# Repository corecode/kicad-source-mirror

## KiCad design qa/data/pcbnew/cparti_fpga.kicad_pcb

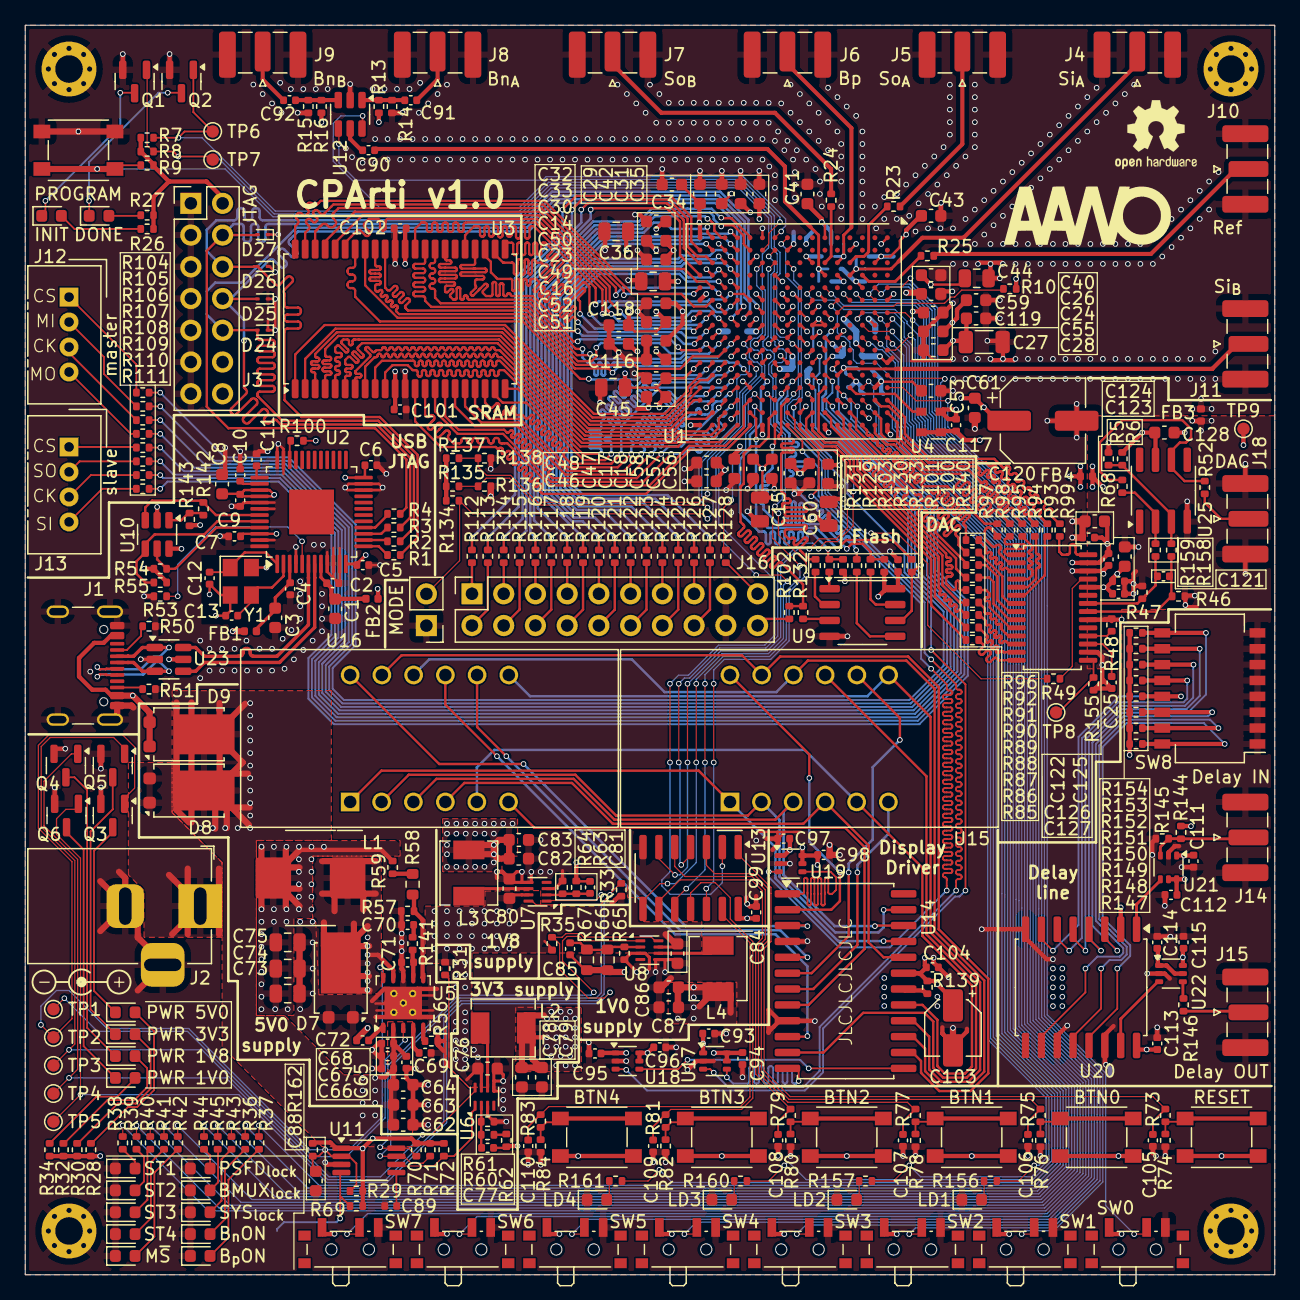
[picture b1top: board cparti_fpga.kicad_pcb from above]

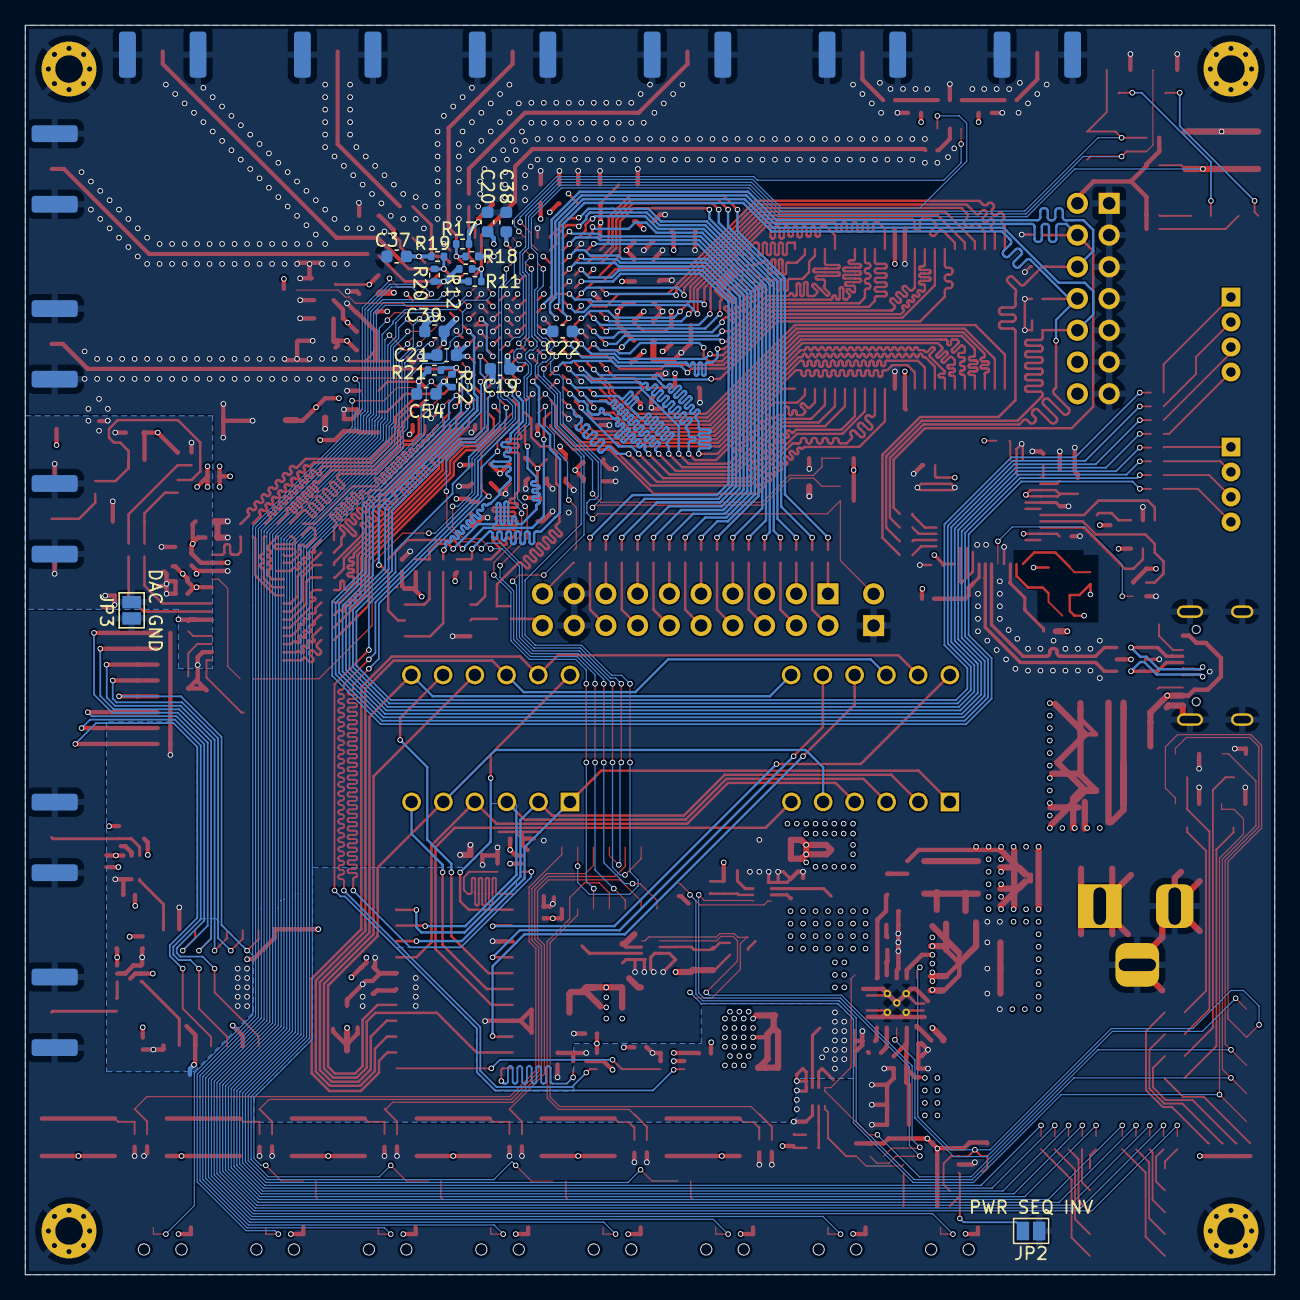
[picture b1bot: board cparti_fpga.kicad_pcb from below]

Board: 4 copper layers, 100.0 x 100.0 mm, 410 parts (18 on the bottom side), 333 nets.

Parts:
BTN0, BTN1, BTN2, BTN3, BTN4: SW_Push; SW_Push_TSC015A035_4.5x4.5mm_H4.5mm
BTN6: RESET; SW_Push_TSC015A035_4.5x4.5mm_H4.5mm
BTN7: PROGRAM; SW_Push_TSC015A035_4.5x4.5mm_H4.5mm
C1, C3, C8, C17, C24, C34, C35, C42, C43, C46, C47, C58, C59, C61, C116, C118: 4.7u; C_0603_1608Metric
C2, C4, C5, C6, C7, C9, C10, C11, C25, C72, C93, C94, C95, C96, C97, C98, C99, C100, C101, C102, C104, C105, C106, C107, C108, C109, C110, C111, C112, C113, C114, C115, C117, C122, C123, C126, C127: 100n; C_0402_1005Metric
C12, C13: 20p; C_0402_1005Metric
C14, C15, C36, C44, C45, C60, C73, C74, C75: 47u; C_0805_2012Metric
C16, C18, C19, C20, C21, C22, C23, C26, C28, C29, C30, C31, C32, C33, C37, C38, C39, C40, C41, C48, C49, C50, C51, C52, C53, C54, C55, C56, C57, C119: 470n; C_0603_1608Metric
C27: 100u; C_1206_3216Metric
C62, C63, C64, C76, C78, C79, C80, C82, C83, C84, C86, C87, C88, C124, C125, C128: 10u; C_0603_1608Metric
C65, C66, C67, C68: 2u2; C_0402_1005Metric
C69, C89, C90, C91, C92: 10n; C_0402_1005Metric
C70: 4n7; C_0402_1005Metric
C71: 47p; C_0402_1005Metric
C77, C81, C85: 120p; C_0402_1005Metric
C103: 10u; CP_Elec_4x5.4
C120: 330u; CP_Elec_6.3x7.7
C121: C_0402_1005Metric
D1: INIT; LED_0603_1608Metric
D2: DONE; LED_0603_1608Metric
D3: PWR 5V0; LED_0603_1608Metric
D4: PWR 3V3; LED_0603_1608Metric
D5: PWR 1V8; LED_0603_1608Metric
D6: PWR 1V0; LED_0603_1608Metric
D7, D8, D9: PDS760; TO-277B
D10: B_{n}ON; LED_0603_1608Metric
D11: B_{p}ON; LED_0603_1608Metric
D12: ST1; LED_0603_1608Metric
D13: ST2; LED_0603_1608Metric
D14: ST3; LED_0603_1608Metric
D15: ST4; LED_0603_1608Metric
D16: M~{S}; LED_0603_1608Metric
D17: SYS_{lock}; LED_0603_1608Metric
D18: PSFD_{lock}; LED_0603_1608Metric
D19: BMUX_{lock}; LED_0603_1608Metric
D20: LD1; LED_0603_1608Metric
D21: LD2; LED_0603_1608Metric
D22: LD3; LED_0603_1608Metric
D23: LD4; LED_0603_1608Metric
D24, D25, D26, D27: ESD9B3.3ST5G; D_SOD-923
FB1, FB2, FB3, FB4: BLM15AG601SN1D; L_0402_1005Metric
H1, H2, H3, H4: MountingHole_Pad; MountingHole_2.2mm_M2_Pad_Via
J1: USB_C_Receptacle_USB2.0_16P; USB_C_Receptacle_GCT_USB4105-xx-A_16P_TopMnt_Horizontal
J2: Barrel_Jack_Switch; BarrelJack_Horizontal
J3: JTAG; PinHeader_2x07_P2.54mm_Vertical
J4: Si_{A}; SMA_Samtec_SMA-J-P-H-ST-EM1_EdgeMount
J5: So_{A}; SMA_Samtec_SMA-J-P-H-ST-EM1_EdgeMount
J6: Bp; SMA_Samtec_SMA-J-P-H-ST-EM1_EdgeMount
J7: So_{B}; SMA_Samtec_SMA-J-P-H-ST-EM1_EdgeMount
J8: Bn_{A}; SMA_Samtec_SMA-J-P-H-ST-EM1_EdgeMount
J9: Bn_{B}; SMA_Samtec_SMA-J-P-H-ST-EM1_EdgeMount
J10: Ref; SMA_Samtec_SMA-J-P-H-ST-EM1_EdgeMount
J11: Si_{B}; SMA_Samtec_SMA-J-P-H-ST-EM1_EdgeMount
J12: master; NS-Tech_Grove_1x04_P2mm_Vertical
J13: slave; NS-Tech_Grove_1x04_P2mm_Vertical
J14: Delay IN; SMA_Samtec_SMA-J-P-H-ST-EM1_EdgeMount
J15: Delay OUT; SMA_Samtec_SMA-J-P-H-ST-EM1_EdgeMount
J16: Conn_02x10_Odd_Even; PinSocket_2x10_P2.54mm_Vertical
J18: DAC; SMA_Samtec_SMA-J-P-H-ST-EM1_EdgeMount
JP1: MODE; PinHeader_1x02_P2.54mm_Vertical
JP2: PWR SEQ INV; SolderJumper-2_P1.3mm_Open_Pad1.0x1.5mm
JP3: DAC GND; SolderJumper-2_P1.3mm_Open_Pad1.0x1.5mm
L1: 6.8uH/6.8A; L_TDK_SPM7054VT
L2, L3, L4: 470nH/7.6A; L_Chilisin_BMRx00040412
NT1, NT2, NT3, NT4: NetTie_2; NetTie-2_SMD_Pad0.2355mm
Q1, Q2, Q3, Q4, Q5, Q6: 2N7002; SOT-23
R1, R2, R3, R4, R49, R85, R86, R87, R88, R89, R90, R91, R92, R93, R94, R95, R96, R97, R98, R99, R104, R105, R106, R107, R108, R109, R110, R111: 22R; R_0402_1005Metric
R5, R6, R26, R27, R28, R30, R32, R34, R59, R128, R134: 1k; R_0402_1005Metric
R7, R36, R37, R38, R39, R40, R41, R42, R43, R44, R45, R156, R157, R160, R161: 330R; R_0402_1005Metric
R8, R9, R10, R103: 4k7; R_0402_1005Metric
R11, R12, R13, R14, R15, R16, R17, R18, R19, R20, R21, R22, R112, R113, R114, R115, R116, R117, R118, R119, R120, R121, R122, R123, R124, R125, R126, R127, R129, R130, R131, R132, R133, R144, R145: 100; R_0402_1005Metric
R23, R24, R25, R52, R135, R136, R137, R138, R146: 0; R_0402_1005Metric
R29, R31, R33, R35, R54, R55, R69, R73, R74, R75, R76, R77, R78, R79, R80, R81, R82, R83, R84, R100, R139, R143, R147, R148, R149, R150, R151, R152, R153, R154, R155: 10k; R_0402_1005Metric
R46, R47: 25R5; R_0402_1005Metric
R48, R101, R102, R142: 2k; R_0402_1005Metric
R50, R51: 5k1; R_0402_1005Metric
R53: 12k/1%; R_0402_1005Metric
R56: 243k; R_0402_1005Metric
R57: 12k; R_0402_1005Metric
R58: 62k; R_0603_1608Metric
R60, R64, R70, R71, R72, R162: 100k; R_0402_1005Metric
R61: 150k; R_0402_1005Metric
R62: 300k; R_0402_1005Metric
R63: 200k; R_0402_1005Metric
R65: 120k; R_0402_1005Metric
R66, R67: 160k; R_0603_1608Metric
R68: 500; R_0402_1005Metric
R140: 49R9; R_0402_1005Metric
R141: 16k9; R_0402_1005Metric
R158, R159: 226; R_0402_1005Metric
SW0, SW1, SW2, SW3, SW4, SW5, SW6, SW7: SW_SPDT; SW_SPDT_PCM12
SW8: SW_DIP_x08; SW_DIP_SPSTx08_Slide_KingTek_DSHP08TS_W7.62mm_P1.27mm
TP1, TP2, TP3, TP4, TP5, TP6, TP7, TP8, TP9: TestPoint; TestPoint_Pad_D1.0mm
U1: XC7A50T-FTG256; Xilinx_FTG256
U2: FT232H; LQFP-48-1EP_7x7mm_P0.5mm_EP3.6x3.6mm
U3: IS61WV25616EDBLL; TSOP-II-44_10.16x18.41mm_P0.8mm
U4: ASDM1-24MHz; Oscillator_SMD_Abracon_ASDMB-4Pin_2.5x2.0mm
U5: TPS54561; Texas_S-PWSON-N10_4x4mm_ThermalVias
U6, U7, U8: TPS62823DLC; Texas_VSON-HR-8_1.5x2mm_P0.5mm
U9: MX25L3233FM1; SOP-8_3.9x4.9mm_P1.27mm
U10: 93LC56BT-I/OT; SOT-23-6
U11: LM3881; Texas_S-PDSO-G8_3x3mm_P0.65mm
U12: AS169-73LF; SOT-23-6
U13: 74HC14; SO-14_3.9x8.65mm_P1.27mm
U14: MAX7219; SOIC-24W_7.5x15.4mm_P1.27mm
U15, U16: XLITX 3641AS; XLITX_3641AS
U17, U18, U19, U21, U22: SN74LVC1T45DCK; SOT-363_SC-70-6
U20: DS1023; SOIC-16W_7.5x10.3mm_P1.27mm
U23: USBLC6-2SC6; SOT-23-6
U24: AD9744; TSSOP-28_4.4x9.7mm_P0.65mm
U25: OPA356AID; SOIC-8_3.9x4.9mm_P1.27mm
Y1: 12 MHz; Crystal_SMD_3225-4Pin_3.2x2.5mm

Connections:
7SEG_{CLK}: U1.H12 (IO_L20P_T3_A20_15), U18.3 (A)
7SEG_{DIN}: U1.J15 (IO_L23P_T3_FOE_B_15), U19.3 (A)
7SEG_{LOAD}: U1.J16 (IO_L23N_T3_FWE_B_15), U17.3 (A)
+1V0: C20.2, C21.2, C22.2, C23.2, C24.2, C27.2, C28.2, C61.2, C85.2, C86.2, C87.2, C118.2, C119.2, C120.1, L4.2, R66.2, R67.2, U1.E10 (VCCBRAM), U1.F7 (VCCINT), U1.F9 (VCCINT), U1.F11 (VCCBRAM), U1.G6 (VCCINT), U1.H9 (VCCINT), U1.J6 (VCCINT), U1.K9 (VCCINT), U1.L8 (VCCINT)
+1V8: C15.2, C16.2, C17.2, C18.2, C19.2, C26.1, C81.2, C82.2, C83.2, C116.2, L3.2, R63.2, U1.F8 (VCCBATT_0), U1.G8 (VCCADC_0), U1.G10 (VCCAUX), U1.J10 (VCCAUX), U1.K11 (VCCAUX), U1.L10 (VCCAUX)
+3.3VA: C125.2, C126.1, C127.1, C128.2, FB4.2, R6.1, TP9.1, U24.24 (AVDD), U25.7 (V+)
+3V3: BTN0.1, BTN1.1, BTN2.1, BTN3.1, BTN4.1, BTN6.1, C5.2, C6.2, C7.2, C8.2, C9.2, C14.1, C29.2, C30.2, C31.2, C32.2, C33.2, C34.2, C35.2, C36.2, C37.2, C38.2, C39.2, C40.2, C41.2, C42.2, C43.2, C44.2, C45.2, C46.2, C47.2, C48.2, C49.2, C50.2, C51.2, C52.2, C53.2, C54.2, C55.2, C56.2, C57.2, C58.2, C59.2, C60.2, C77.2, C78.2, C79.2, C93.2, C95.2, C97.2, C99.2, C100.2, C101.2, C102.2, C111.2, C115.2, C117.2, C122.1, C123.1, C124.2, FB1.1, FB2.1, FB4.1, J3.2, J16.19, J16.20, L2.2, R7.2, R8.2, R9.2, R10.2, R11.1, R13.1, R15.1, R17.1, R19.1, R21.1, R26.2, R27.2, R28.2, R30.2, R32.2, R34.2, R54.1, R55.1, R62.2, R100.2, R101.2, R102.2, R103.2, R128.1, R134.2, R135.1, R137.1, R143.1, R144.1, SW0.1 (A), SW1.1 (A), SW2.1 (A), SW3.1 (A), SW4.1 (A), SW5.1 (A), SW6.1 (A), SW7.1 (A), U1.A6 (VCCO_35), U1.A16 (VCCO_15), U1.B3 (VCCO_35), U1.B13 (VCCO_15), U1.C10 (VCCO_15), U1.D7 (VCCO_35), U1.E4 (VCCO_35), U1.E14 (VCCO_15), U1.F1 (VCCO_35), U1.H15 (VCCO_15), U1.J2 (VCCO_35), U1.J12 (VCCO_15), U1.L6 (VCCO_0), U1.L16 (VCCO_14), U1.M3 (VCCO_34), U1.M13 (VCCO_14), U1.N10 (VCCO_14), U1.P7 (VCCO_14), U1.R4 (VCCO_34), U1.R14 (VCCO_14), U1.T1 (VCCO_34), U1.T11 (VCCO_14), U2.12 (VCCIO), U2.24 (VCCIO), U2.39 (VCCD), U2.40 (VREGIN), U2.46 (VCCIO), U3.11 (VDD), U3.33 (VDD), U4.1 (Standby), U4.4 (VDD), U9.8 (VCC), U10.6 (VCC), U13.14 (VCC), U17.1 (VCCA), U18.1 (VCCA), U19.1 (VCCA), U21.1 (VCCA), U22.6 (VCCB), U24.27 (DVDD)
+5V: C73.2, C74.2, C75.2, C76.2, C80.2, C84.2, C94.2, C96.2, C98.2, C103.1, C104.2, C112.2, C113.2, C114.2, L1.2, R29.1, R31.1, R33.1, R35.1, R59.2, R69.2, R70.2, R71.2, R72.2, R139.1, R147.2, R148.2, R149.2, R150.2, R151.2, R152.2, R153.2, R154.2, R162.2, U6.7 (VIN), U7.7 (VIN), U8.7 (VIN), U11.1 (VCC), U14.19 (V+), U17.5 (DIR), U17.6 (VCCB), U18.5 (DIR), U18.6 (VCCB), U19.5 (DIR), U19.6 (VCCB), U20.2 (LE), U20.16 (VCC), U21.5 (DIR), U21.6 (VCCB), U22.1 (VCCA), U22.5 (DIR)
/DAC/DAC_OPAMP_O: R52.2, R68.2, U25.6
/DAC/DAC_OPAMP_O_R: J18.1 (In), R52.1
/DAC/IOUTA: C121.2, R47.1, R159.1, U24.22 (IOUTA)
/DAC/IOUTA_R: R68.1, R159.2, U25.2 (-)
/DAC/IOUTB: C121.1, R46.1, R158.1, U24.21 (IOUTB)
/DAC/IOUTB_R: R5.2, R6.2, R158.2, U25.3 (+)
/DAC/R_DAC_CLK: R99.2, U24.28 (CLK)
/DAC/R_DAC_D0: R85.2, U24.14 (D0)
/DAC/R_DAC_D1: R86.2, U24.13 (D1)
/DAC/R_DAC_D2: R87.2, U24.12 (D2)
/DAC/R_DAC_D3: R88.2, U24.11 (D3)
/DAC/R_DAC_D4: R89.2, U24.10 (D4)
/DAC/R_DAC_D5: R90.2, U24.9 (D5)
/DAC/R_DAC_D6: R91.2, U24.8 (D6)
/DAC/R_DAC_D7: R92.2, U24.7 (D7)
/DAC/R_DAC_D8: R93.2, U24.6 (D8)
/DAC/R_DAC_D9: R94.2, U24.5 (D9)
/DAC/R_DAC_D10: R95.2, U24.4 (D10)
/DAC/R_DAC_D11: R96.2, U24.3 (D11)
/DAC/R_DAC_D12: R97.2, U24.2 (D12)
/DAC/R_DAC_D13: R98.2, U24.1 (D13)
/DAC/R_DAC_MODE: R49.2, U24.25 (MODE)
/DAC/SLEEP: R155.2, TP8.1, U24.15 (SLEEP)
/FPGA banks 14-15/EMCCLK: R140.2, U1.M15 (IO_L3N_T0_DQS_EMCCLK_14)
/FPGA banks 14-15/SPIm_MISO_R: J12.2, R105.2
/FPGA banks 14-15/SPIm_MOSI_R: J12.4, R107.2
/FPGA banks 14-15/SPIm_SCK_R: J12.3, R106.2
/FPGA banks 14-15/SPIm_~CS_R: J12.1, R104.2
/FPGA banks 14-15/SPIs_MISO_R: J13.2, R109.2
/FPGA banks 14-15/SPIs_MOSI_R: J13.4, R111.2
/FPGA banks 14-15/SPIs_SCK_R: J13.3, R110.2
/FPGA banks 14-15/SPIs_~CS_R: J13.1, R108.2
/FPGA banks 34-35/IO_0: R112.1, U1.T2 (IO_L8N_T1_34)
/FPGA banks 34-35/IO_0_R: J16.1, R112.2
/FPGA banks 34-35/IO_1: R113.1, U1.R3 (IO_L8P_T1_34)
/FPGA banks 34-35/IO_1_R: J16.2, R113.2
/FPGA banks 34-35/IO_2: R114.1, U1.T3 (IO_L9N_T1_DQS_34)
/FPGA banks 34-35/IO_2_R: J16.3, R114.2
/FPGA banks 34-35/IO_3: R115.1, U1.T4 (IO_L9P_T1_DQS_34)
/FPGA banks 34-35/IO_3_R: J16.4, R115.2
/FPGA banks 34-35/IO_4: R116.1, U1.M1 (IO_L2N_T0_34)
/FPGA banks 34-35/IO_4_R: J16.5, R116.2
/FPGA banks 34-35/IO_5: R117.1, U1.M2 (IO_L2P_T0_34)
/FPGA banks 34-35/IO_5_R: J16.6, R117.2
/FPGA banks 34-35/IO_6: R118.1, U1.P1 (IO_L4N_T0_34)
/FPGA banks 34-35/IO_6_R: J16.7, R118.2
/FPGA banks 34-35/IO_7: R119.1, U1.R1 (IO_L7N_T1_34)
/FPGA banks 34-35/IO_7_R: J16.8, R119.2
/FPGA banks 34-35/IO_8: R120.1, U1.N1 (IO_L4P_T0_34)
/FPGA banks 34-35/IO_8_R: J16.9, R120.2
/FPGA banks 34-35/IO_9: R121.1, U1.N2 (IO_L3N_T0_DQS_34)
/FPGA banks 34-35/IO_9_R: J16.10, R121.2
/FPGA banks 34-35/IO_10: R122.1, U1.R2 (IO_L7P_T1_34)
/FPGA banks 34-35/IO_10_R: J16.11, R122.2
/FPGA banks 34-35/IO_11: R123.1, U1.N3 (IO_L3P_T0_DQS_34)
/FPGA banks 34-35/IO_11_R: J16.12, R123.2
/FPGA banks 34-35/IO_12: R124.1, U1.P3 (IO_L5N_T0_34)
/FPGA banks 34-35/IO_12_R: J16.13, R124.2
/FPGA banks 34-35/IO_13: R125.1, U1.N4 (IO_L6N_T0_VREF_34)
/FPGA banks 34-35/IO_13_R: J16.14, R125.2
/FPGA banks 34-35/IO_14: R126.1, U1.P4 (IO_L5P_T0_34)
/FPGA banks 34-35/IO_14_R: J16.15, R126.2
/FPGA banks 34-35/IO_15: R127.1, U1.P5 (IO_L10P_T1_34)
/FPGA banks 34-35/IO_15_R: J16.16, R127.2
/High frequency/Bn_{A}_C_SMA: C91.2, J8.1 (In)
/High frequency/Bn_{A}_SMA: C91.1, R13.2, R14.1, U12.1 (J3)
/High frequency/Bn_{B}_C_SMA: C92.2, J9.1 (In)
/High frequency/Bn_{B}_SMA: C92.1, R15.2, R16.1, U12.3 (J2)
/High frequency/HF_Bn_C_SMA: C90.2, U12.5 (J1)
/High frequency/HF_Bn_R_SMA: C90.1, NT1.2
/High frequency/HF_Bp_R_SMA: J6.1 (In), NT2.2
/High frequency/HF_Ref_R_SMA: J10.1 (In), R25.1
/High frequency/HF_Si_A_R_SMA: J4.1 (In), NT3.2
/High frequency/HF_Si_B_R_SMA: J11.1 (In), NT4.2
/High frequency/HF_So_A_R_SMA: J5.1 (In), R23.1
/High frequency/HF_So_B_R_SMA: J7.1 (In), R24.1
/LEDs/7SEG_{CLK}_5V: U14.13 (CLK), U18.4 (B)
/LEDs/7SEG_{DIN}_5V: U14.1 (DIN), U19.4 (B)
/LEDs/7SEG_{LOAD}_5V: U14.12 (LOAD), U17.4 (B)
/LEDs/DIG_0: U14.2 (DIG_0), U15.12 (CC1)
/LEDs/DIG_1: U14.11 (DIG_1), U15.9 (CC2)
/LEDs/DIG_2: U14.6 (DIG_2), U15.8 (CC3)
/LEDs/DIG_3: U14.7 (DIG_3), U15.6 (CC4)
/LEDs/DIG_4: U14.3 (DIG_4), U16.12 (CC1)
/LEDs/DIG_5: U14.10 (DIG_5), U16.9 (CC2)
/LEDs/DIG_6: U14.5 (DIG_6), U16.8 (CC3)
/LEDs/DIG_7: U14.8 (DIG_7), U16.6 (CC4)
/LEDs/SEG_A: U14.14 (SEG_A), U15.11 (a), U16.11 (a)
/LEDs/SEG_B: U14.16 (SEG_B), U15.7 (b), U16.7 (b)
/LEDs/SEG_C: U14.20 (SEG_C), U15.4 (c), U16.4 (c)
/LEDs/SEG_D: U14.23 (SEG_D), U15.2 (d), U16.2 (d)
/LEDs/SEG_DP: U14.22 (SEG_DP), U15.3 (DPX), U16.3 (DPX)
/LEDs/SEG_E: U14.21 (SEG_E), U15.1 (e), U16.1 (e)
/LEDs/SEG_F: U14.15 (SEG_F), U15.10 (f), U16.10 (f)
/LEDs/SEG_G: U14.17 (SEG_G), U15.5 (g), U16.5 (g)
/Power/PG_1V0: Q6.1 (G), R35.2, TP5.1, U8.8 (PG)
/Power/PG_1V8: Q4.1 (G), R33.2, TP4.1, U7.8 (PG)
/Power/PG_3V3: Q5.1 (G), R31.2, TP3.1, U6.8 (PG)
/Power/PG_5V0: C88.2, Q3.1 (G), R29.2, R162.1, TP2.1, U5.10 (PWRGD), U11.2 (EN)
/Power/SW_5V: C72.1, D7.3 (K), L1.1, U5.9 (SW)
/Power/VCC_1V0_en: R70.1, U8.1 (EN), U11.8 (FLAG1)
/Power/VCC_1V8_en: R71.1, U7.1 (EN), U11.7 (FLAG2)
/Power/VCC_3V3_en: R72.1, U6.1 (EN), U11.6 (FLAG3)
/Programmable delay/DelayIN_50Ohm: J14.1 (In), R144.2, R145.1, U21.3 (A)
/Programmable delay/DelayIN_{5V}_50Ohm: U20.1 (IN), U21.4 (B)
/Programmable delay/DelayOUT_50Ohm: J15.1 (In), R146.1
/Programmable delay/DelayOUT_R_50Ohm: R146.2, U22.4 (B)
/Programmable delay/DelayOUT_{5V}_50Ohm: U20.15 (OUT/~OUT), U22.3 (A)
/Programmable delay/P0: R154.1, SW8.9, U20.3 (P0/Q)
/Programmable delay/P1: R153.1, SW8.10, U20.4 (P1/CLK)
/Programmable delay/P2: R152.1, SW8.11, U20.5 (P2/D)
/Programmable delay/P3: R151.1, SW8.12, U20.6 (P3)
/Programmable delay/P4: R150.1, SW8.13, U20.7 (P4)
/Programmable delay/P5: R149.1, SW8.14, U20.10 (P5)
/Programmable delay/P6: R148.1, SW8.15, U20.12 (P6)
/Programmable delay/P7: R147.1, SW8.16, U20.13 (P7)
/USB/EECLK: R55.2, U2.44 (EECLK), U10.4 (CLK)
/USB/EECS: R54.2, U2.45 (EECS), U10.5 (CS)
/USB/EEDATA: R142.2, U2.43 (EEDATA), U10.3 (DI)
/USB/JTAG_R_TCK: R1.1, U2.13 (ADBUS0)
/USB/JTAG_R_TDI: R2.1, U2.14 (ADBUS1)
/USB/JTAG_R_TDO: R3.1, U2.15 (ADBUS2)
/USB/JTAG_R_TMS: R4.1, U2.16 (ADBUS3)
/USB/USB_D+: J1.A6 (D+), J1.B6 (D+), U23.3 (I/O2)
/USB/USB_D-: J1.A7 (D-), J1.B7 (D-), U23.1 (I/O1)
/USB/USB_D_N: U2.6 (DM), U23.6 (I/O1)
/USB/USB_D_P: U2.7 (DP), U23.4 (I/O2)
/config/CFGBVS: R10.1, U1.E7 (CFGBVS_0)
/config/DONE: Q2.1 (G), R7.1, TP6.1, U1.H10 (DONE_0)
/config/INIT: Q1.1 (G), R8.1, TP7.1, U1.K10 (INIT_B_0)
/config/MODE0: R137.2, R138.1, U1.M9 (M0_0)
/config/MODE1: R135.2, R136.1, U1.M10 (M1_0)
/config/MODE2: JP1.2 (B), R134.1, U1.M11 (M2_0)
/config/PROGRAM: BTN7.1, R9.1, U1.L9 (PROGRAM_B_0)
BMUX_{lock}: R45.1, U1.A9 (IO_L2N_T0_AD8N_15)
BTN0: U1.J3 (IO_L21P_T3_DQS_35), U13.4
BTN1: U1.J1 (IO_L22N_T3_35), U13.6
BTN2: U1.L3 (IO_L23P_T3_35), U13.8
BTN3: U1.K3 (IO_L24P_T3_35), U13.10
BTN4: U1.K2 (IO_L24N_T3_35), U13.12
BTN_RST: U1.L14 (IO_L4P_T0_D04_14), U13.2
B_{n}ON: R36.1, U1.B9 (IO_L3P_T0_DQS_AD1P_15)
B_{p}ON: R37.1, U1.C9 (IO_L1N_T0_AD0N_15)
DAC_CLK: R99.1, U1.A14 (IO_L7N_T1_AD2N_15)
DAC_D0: R85.1, U1.H16 (IO_L22P_T3_A17_15)
DAC_D1: R86.1, U1.G15 (IO_L24N_T3_RS0_15)
DAC_D2: R87.1, U1.G16 (IO_L22N_T3_A16_15)
DAC_D3: R88.1, U1.F13 (IO_L16N_T2_A27_15)
DAC_D4: R89.1, U1.F15 (IO_L18P_T2_A24_15)
DAC_D5: R90.1, U1.E16 (IO_L17P_T2_A26_15)
DAC_D6: R91.1, U1.E15 (IO_L18N_T2_A23_15)
DAC_D7: R92.1, U1.D16 (IO_L17N_T2_A25_15)
DAC_D8: R93.1, U1.B14 (IO_L8N_T1_AD10N_15)
DAC_D9: R94.1, U1.A15 (IO_L9N_T1_DQS_AD3N_15)
DAC_D10: R95.1, U1.B15 (IO_L9P_T1_DQS_AD3P_15)
DAC_D11: R96.1, U1.D15 (IO_L15N_T2_DQS_ADV_B_15)
DAC_D12: R97.1, U1.C16 (IO_L10P_T1_AD11P_15)
DAC_D13: R98.1, U1.B16 (IO_L10N_T1_AD11N_15)
DAC_MODE: R49.1, U1.H13 (IO_L20N_T3_A19_15)
FPGA_CFG_CS: R103.1, R129.1, U1.L12 (IO_L6P_T0_FCS_B_14)
FPGA_CFG_D0: R130.1, U1.J13 (IO_L1P_T0_D00_MOSI_14)
FPGA_CFG_D1: R131.1, U1.J14 (IO_L1N_T0_D01_DIN_14)
FPGA_CFG_D2: R102.1, R132.1, U1.K15 (IO_L2P_T0_D02_14)
FPGA_CFG_D3: R101.1, R133.1, U1.K16 (IO_L2N_T0_D03_14)
FPGA_CFG_SCK: R140.1, U1.E8 (CCLK_0), U9.6 (SCLK)
GCLK_24MHz: U1.D13 (IO_L12P_T1_MRCC_15), U4.3 (Out)
GND: BTN7.2, C1.1, C2.1, C3.1, C4.1, C5.1, C6.1, C7.1, C8.1, C9.1, C10.1, C11.1, C12.1, C13.1, C14.2, C15.1, C16.1, C17.1, C18.1, C19.1, C20.1, C21.1, C22.1, C23.1, C24.1, C26.2, C27.1, C28.1, C29.1, C30.1, C31.1, C32.1, C33.1, C34.1, C35.1, C36.1, C37.1, C38.1, C39.1, C40.1, C41.1, C42.1, C43.1, C44.1, C45.1, C46.1, C47.1, C48.1, C49.1, C50.1, C51.1, C52.1, C53.1, C54.1, C55.1, C56.1, C57.1, C58.1, C59.1, C60.1, C61.1, C62.1, C63.1, C64.1, C65.1, C66.1, C67.1, C68.1, C69.1, C70.1, C71.1, C73.1, C74.1, C75.1, C76.1, C78.1, C79.1, C80.1, C82.1, C83.1, C84.1, C86.1, C87.1, C88.1, C89.1, C93.1, C94.1, C95.1, C96.1, C97.1, C98.1, C99.1, C100.1, C101.1, C102.1, C103.2, C104.1, C105.1, C106.1, C107.1, C108.1, C109.1, C110.1, C111.1, C112.1, C113.1, C114.1, C115.1, C116.1, C117.1, C118.1, C119.1, C120.2, C122.2, C123.2, C124.1, D7.1 (A), D7.2 (A), D10.1 (K), D11.1 (K), D12.1 (K), D13.1 (K), D14.1 (K), D15.1 (K), D16.1 (K), D17.1 (K), D18.1 (K), D19.1 (K), D20.1 (K), D21.1 (K), D22.1 (K), D23.1 (K), D24.1 (A1), D25.1 (A1), D26.1 (A1), D27.1 (A1), FB3.1, H1.1, H2.1, H3.1, H4.1, J1.A1 (GND), J1.A12 (GND), J1.B1 (GND), J1.B12 (GND), J1.S1 (SHIELD), J2.2, J2.3, J3.1, J3.3, J3.5, J3.7, J3.9, J3.11, J3.13, J4.2 (Ext), J5.2 (Ext), J6.2 (Ext), J7.2 (Ext), J8.2 (Ext), J9.2 (Ext), J10.2 (Ext), J11.2 (Ext), J14.2 (Ext), J15.2 (Ext), J16.17, J16.18, JP1.1 (A), JP2.1 (A), JP3.1 (A), Q1.2 (S), Q2.2 (S), Q3.2 (S), Q4.2 (S), Q5.2 (S), Q6.2 (S), R12.2, R14.2, R16.2, R18.2, R20.2, R22.2, R50.2, R51.2, R53.1, R56.2, R57.2, R60.1, R64.1, R65.1, R74.2, R76.2, R78.2, R80.2, R82.2, R84.2, R136.2, R138.2, R145.2, SW0.3 (C), SW1.3 (C), SW2.3 (C), SW3.3 (C), SW4.3 (C), SW5.3 (C), SW6.3 (C), SW7.3 (C), SW8.1, SW8.2, SW8.3, SW8.4, SW8.5, SW8.6, SW8.7, SW8.8, U1.A1 (GND), U1.A11 (GND), U1.B8 (GND), U1.C5 (GND), U1.C15 (GND), U1.D2 (GND), U1.D12 (GND), U1.E9 (GND), U1.F6 (GND), U1.F10 (GND), U1.F16 (GND), U1.G3 (GND), U1.G7 (GNDADC_0), U1.G9 (GND), U1.G13 (GND), U1.H6 (GND), U1.H7 (VREFN_0), U1.H8 (VP_0), U1.J7 (VN_0), U1.J8 (VREFP_0), U1.J9 (GND), U1.J11 (GND), U1.K4 (GND), U1.K6 (GND), U1.K7 (DXN_0), U1.K8 (DXP_0), U1.K14 (GND), U1.L1 (GND), U1.L11 (GND), U1.M8 (GND), U1.N5 (GND), U1.N15 (GND), U1.P2 (GND), U1.P12 (GND), U1.R9 (GND), U1.T6 (GND), U1.T16 (GND), U2.4 (AGND), U2.9 (AGND), U2.10 (GND), U2.11 (GND), U2.22 (GND), U2.23 (GND), U2.35 (GND), U2.36 (GND), U2.41 (AGND), U2.42 (TEST), U2.47 (GND), U2.48 (GND), U3.12 (GND), U3.34 (GND), U4.2 (GND), U5.8 (GND), U5.11 (GND), U6.3 (AGND), U6.5 (PGND), U7.3 (AGND), U7.5 (PGND), U8.3 (AGND), U8.5 (PGND), U9.4 (GND), U10.2 (GND), U11.3 (GND), U12.2 (GND), U13.7 (GND), U14.4 (GND), U14.9 (GND), U17.2 (GND), U18.2 (GND), U19.2 (GND), U20.8 (GND), U20.11 (MS), U20.14 (~P/S), U21.2 (GND), U22.2 (GND), U23.2 (GND), U24.26 (DGND), Y1.2, Y1.4
GNDA: C25.2, C125.1, C126.2, C127.2, C128.1, FB3.2, J18.2 (Ext), JP3.2 (B), R5.1, R46.2, R47.2, R48.1, R155.1, U24.16 (REFLO), U24.20 (AGND), U25.4 (V-)
HF_Bn_50Ohm: NT1.1, R11.2, R12.1, U1.F4 (IO_L14P_T2_SRCC_35)
HF_Bn_ctrl_V1: U1.K1 (IO_L22P_T3_35), U12.4 (V1)
HF_Bn_ctrl_V2: U1.L2 (IO_L23N_T3_35), U12.6 (V2)
HF_Bp_50Ohm: NT2.1, R17.2, R18.1, U1.E3 (IO_L11P_T1_SRCC_35)
HF_Ref_50Ohm: R25.2, U1.C4 (IO_L12N_T1_MRCC_35)
HF_Si_A_50Ohm: NT3.1, R19.2, R20.1, U1.D4 (IO_L12P_T1_MRCC_35)
HF_Si_B_50Ohm: NT4.1, R21.2, R22.1, U1.E12 (IO_L13P_T2_MRCC_15)
HF_So_A_50Ohm: R23.2, U1.D3 (IO_L11N_T1_SRCC_35)
HF_So_B_50Ohm: R24.2, U1.F3 (IO_L14N_T2_SRCC_35)
JTAG_TCK: D26.2 (A2), J3.6, R1.2, U1.L7 (TCK_0)
JTAG_TDI: D24.2 (A2), J3.10, R2.2, U1.N7 (TDI_0)
JTAG_TDO: D25.2 (A2), J3.8, R3.2, U1.N8 (TDO_0)
JTAG_TMS: D27.2 (A2), J3.4, R4.2, U1.M7 (TMS_0)
LED1: R156.1, U1.D14 (IO_L15P_T2_DQS_15)
LED2: R157.1, U1.C14 (IO_L8P_T1_AD10P_15)
LED3: R160.1, U1.C13 (IO_L12N_T1_MRCC_15)
LED4: R161.1, U1.E6 (IO_0_35)
M~S: R42.1, U1.A8 (IO_L2P_T0_AD8P_15)
unnamed: BTN0.2, R75.1, R76.1
unnamed: BTN1.2, R77.1, R78.1
unnamed: BTN2.2, R79.1, R80.1
unnamed: BTN3.2, R81.1, R82.1
unnamed: BTN4.2, R83.1, R84.1
unnamed: BTN6.2, R73.1, R74.1
unnamed: C70.2, R141.2
unnamed: C105.2, R73.2, U13.1
unnamed: C106.2, R75.2, U13.3
unnamed: C107.2, R77.2, U13.5
unnamed: C108.2, R79.2, U13.9
unnamed: C109.2, R81.2, U13.11
unnamed: C110.2, R83.2, U13.13
unnamed: D1.2 (A), R26.1
unnamed: D1.1 (K), Q1.3 (D)
unnamed: D2.2 (A), R27.1
unnamed: D2.1 (K), Q2.3 (D)
unnamed: D3.2 (A), R28.1
unnamed: D3.1 (K), Q3.3 (D)
unnamed: D4.2 (A), R30.1
unnamed: D4.1 (K), Q5.3 (D)
unnamed: D5.2 (A), R32.1
unnamed: D5.1 (K), Q4.3 (D)
unnamed: D6.2 (A), R34.1
unnamed: D6.1 (K), Q6.3 (D)
unnamed: D10.2 (A), R36.2
unnamed: D11.2 (A), R37.2
unnamed: D12.2 (A), R38.2
unnamed: D13.2 (A), R39.2
unnamed: D14.2 (A), R40.2
unnamed: D15.2 (A), R41.2
unnamed: D16.2 (A), R42.2
unnamed: D17.2 (A), R43.2
unnamed: D18.2 (A), R44.2
unnamed: D19.2 (A), R45.2
unnamed: D20.2 (A), R156.2
unnamed: D21.2 (A), R157.2
unnamed: D22.2 (A), R160.2
unnamed: D23.2 (A), R161.2
unnamed: J1.A5 (CC1), R50.1
unnamed: J1.B5 (CC2), R51.1
unnamed: JP2.2 (B), R69.1, U11.4 (INV)
unnamed: R58.1, R59.1
unnamed: R61.2, R62.1
unnamed: R128.2, U1.L15 (IO_L3P_T0_DQS_PUDC_B_14)
unnamed: R53.2, U2.5 (REF)
unnamed: C11.2, U2.37 (VCCA)
unnamed: C10.2, U2.38 (VCCCORE)
unnamed: C3.2, C4.2, FB1.2, U2.3 (VPHY)
unnamed: C1.2, C2.2, FB2.2, U2.8 (VPLL)
unnamed: C12.2, U2.1 (XCSI), Y1.1
unnamed: C13.2, U2.2 (XCSO), Y1.3
unnamed: R100.1, U2.34 (~RESET)
unnamed: C72.2, U5.1 (BOOT)
unnamed: C71.2, R141.1, U5.7 (COMP)
unnamed: TP1.1, U5.3 (EN)
unnamed: R57.1, R58.2, U5.6 (FB)
unnamed: R56.1, U5.5 (RT/CLK)
unnamed: C69.2, U5.4 (SS/TR)
unnamed: C77.1, R60.2, R61.1, U6.2 (FB)
unnamed: L2.1, U6.6 (SW)
unnamed: C81.1, R63.1, R64.2, U7.2 (FB)
unnamed: L3.1, U7.6 (SW)
unnamed: C85.1, R65.2, R66.1, R67.1, U8.2 (FB)
unnamed: L4.1, U8.6 (SW)
unnamed: R130.2, U9.5 (SI/SIO0)
unnamed: R131.2, U9.2 (SO/SIO1)
unnamed: R129.2, U9.1 (~CS)
unnamed: R133.2, U9.7 (~HOLD/SIO3)
unnamed: R132.2, U9.3 (~WP/SIO2)
unnamed: R142.1, R143.2, U10.1 (DO)
unnamed: C89.2, U11.5 (TADJ)
unnamed: R139.2, U14.18 (ISET)
unnamed: R48.2, U24.18 (FS_ADJ)
unnamed: C25.1, U24.17 (REFIO)
PSFD_{lock}: R44.1, U1.C8 (IO_L1P_T0_AD0P_15)
SPIm_MISO: R105.1, U1.G14 (IO_L21P_T3_DQS_15)
SPIm_MOSI: R107.1, U1.G12 (IO_L19N_T3_A21_VREF_15)
SPIm_SCK: R106.1, U1.G11 (IO_25_15)
SPIm_~CS: R104.1, U1.H14 (IO_L24P_T3_RS1_15)
SPIs_MISO: R109.1, U1.F14 (IO_L21N_T3_DQS_A18_15)
SPIs_MOSI: R111.1, U1.E13 (IO_L13N_T2_MRCC_15)
SPIs_SCK: R110.1, U1.E11 (IO_L14P_T2_SRCC_15)
SPIs_~CS: R108.1, U1.F12 (IO_L16P_T2_A28_15)
SRAM_A0: U1.T12 (IO_L15N_T2_DQS_DOUT_CSO_B_14), U3.1 (A0)
SRAM_A1: U1.R12 (IO_L15P_T2_DQS_RDWR_B_14), U3.2 (A1)
SRAM_A2: U1.T13 (IO_L16N_T2_A15_D31_14), U3.3 (A2)
SRAM_A3: U1.T14 (IO_L10P_T1_D14_14), U3.4 (A3)
SRAM_A4: U1.T15 (IO_L10N_T1_D15_14), U3.5 (A4)
SRAM_A5: U1.P13 (IO_L11N_T1_SRCC_14), U3.18 (A5)
SRAM_A6: U1.R13 (IO_L16P_T2_CSI_B_14), U3.19 (A6)
SRAM_A7: U1.N12 (IO_L13N_T2_MRCC_14), U3.20 (A7)
SRAM_A8: U1.N11 (IO_L13P_T2_MRCC_14), U3.21 (A8)
SRAM_A9: U1.P11 (IO_L14N_T2_SRCC_14), U3.22 (A9)
SRAM_A10: U1.R7 (IO_L24N_T3_A00_D16_14), U3.23 (A10)
SRAM_A11: U1.T8 (IO_L21N_T3_DQS_A06_D22_14), U3.24 (A11)
SRAM_A12: U1.R8 (IO_L20N_T3_A07_D23_14), U3.25 (A12)
SRAM_A13: U1.T9 (IO_L22P_T3_A05_D21_14), U3.26 (A13)
SRAM_A14: U1.M6 (IO_L19P_T3_A10_D26_14), U3.27 (A14)
SRAM_A15: U1.T5 (IO_L23N_T3_A02_D18_14), U3.42 (A15)
SRAM_A16: U1.R6 (IO_L24P_T3_A01_D17_14), U3.43 (A16)
SRAM_A17: U1.R5 (IO_L23P_T3_A03_D19_14), U3.44 (A17)
SRAM_CE: U1.R15 (IO_L9P_T1_DQS_14), U3.6 (~CE)
SRAM_D0: U1.R16 (IO_L9N_T1_DQS_D13_14), U3.7 (I/O0)
SRAM_D1: U1.P15 (IO_L8P_T1_D11_14), U3.8 (I/O1)
SRAM_D2: U1.P16 (IO_L8N_T1_D12_14), U3.9 (I/O2)
SRAM_D3: U1.N16 (IO_L7N_T1_D10_14), U3.10 (I/O3)
SRAM_D4: U1.M16 (IO_L7P_T1_D09_14), U3.13 (I/O4)
SRAM_D5: U1.M14 (IO_L4N_T0_D05_14), U3.14 (I/O5)
SRAM_D6: U1.N14 (IO_L12P_T1_MRCC_14), U3.15 (I/O6)
SRAM_D7: U1.P14 (IO_L12N_T1_MRCC_14), U3.16 (I/O7)
SRAM_D8: U1.T10 (IO_L22N_T3_A04_D20_14), U3.29 (I/O8)
SRAM_D9: U1.N9 (IO_L18P_T2_A12_D28_14), U3.30 (I/O9)
SRAM_D10: U1.P9 (IO_L18N_T2_A11_D27_14), U3.31 (I/O10)
SRAM_D11: U1.N6 (IO_L19N_T3_A09_D25_VREF_14), U3.32 (I/O11)
SRAM_D12: U1.R10 (IO_L17P_T2_A14_D30_14), U3.35 (I/O12)
SRAM_D13: U1.P10 (IO_L14P_T2_SRCC_14), U3.36 (I/O13)
SRAM_D14: U1.M12 (IO_L6N_T0_D08_VREF_14), U3.37 (I/O14)
SRAM_D15: U1.R11 (IO_L17N_T2_A13_D29_14), U3.38 (I/O15)
SRAM_LB: U1.T7 (IO_L21P_T3_DQS_14), U3.39 (~LB)
SRAM_OE: U1.P6 (IO_25_14), U3.41 (~OE)
SRAM_UB: U1.P8 (IO_L20P_T3_A08_D24_14), U3.40 (~UB)
SRAM_WE: U1.N13 (IO_L11P_T1_SRCC_14), U3.17 (~WE)
SW0: SW0.2 (B), U1.A13 (IO_L7P_T1_AD2P_15)
SW1: SW1.2 (B), U1.A12 (IO_L5N_T0_AD9N_15)
SW2: SW2.2 (B), U1.A5 (IO_L3P_T0_DQS_AD5P_35)
SW3: SW3.2 (B), U1.B6 (IO_L2P_T0_AD12P_35)
SW4: SW4.2 (B), U1.B5 (IO_L2N_T0_AD12N_35)
SW5: SW5.2 (B), U1.C6 (IO_L5N_T0_AD13N_35)
SW6: SW6.2 (B), U1.D6 (IO_L6P_T0_35)
SW7: SW7.2 (B), U1.F5 (IO_L13P_T2_MRCC_35)
SYS_{lock}: R43.1, U1.B7 (IO_L1P_T0_AD4P_35)
Stage1: R38.1, U1.A7 (IO_L1N_T0_AD4N_35)
Stage2: R39.1, U1.G5 (IO_L16P_T2_35)
Stage3: R40.1, U1.A10 (IO_L3N_T0_DQS_AD1N_15)
Stage4: R41.1, U1.C7 (IO_L5P_T0_AD13P_35)
VBUS: D9.1 (A), D9.2 (A), J1.A4 (VBUS), J1.A9 (VBUS), J1.B4 (VBUS), J1.B9 (VBUS), U23.5 (VBUS)
VDC: D8.1 (A), D8.2 (A), J2.1
VDD: C62.2, C63.2, C64.2, C65.2, C66.2, C67.2, C68.2, D8.3 (K), D9.3 (K), U5.2 (VIN)

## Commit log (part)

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2015-05-27 correctly print footprint text on non-silkscreen layers
2015-05-27 obey high contrast mode for pcb and module text
2015-09-28 sexpr export: always quote strings
    Properly quoting strings is required to produce lisp reader compatible
    s-expressions. Quoting does not hurt anything and makes the format more
    uniform, leading to better interoperability with other tools.
2015-11-08 drc: simplify pad DRC
    This simplifies the pad DRC significantly and fixes a bug when two pads
    are close to each other in a right angle, when the edge distances are
    below the clearance, but the corner distance is actually above the
    clearance:
    +---..
    |
2016-01-09 SVG plot: output invisible text in addition to plotting
2017-09-24 Do not consider non-copper pads for connectivity
2019-07-24 kicad2step: scale models
2019-07-24 3d canvas: use radius, not width for circles
2019-07-24 3d: min dot needs to be square
    Given that we compare the dot product (square of length) to s_min_dot,
    it means that s_min_dot also needs to be square, or we wind up
    converting line segments into circles that are visually distinct from
    circles, leading to gaps in polylines.
2019-11-21 start eeschema python
2026-02-13 Fix mathplot double buffer rendering on HiDPI displays
2026-02-13 WIP: Add PDN impedance analyzer to Eeschema
2026-02-16 Add FastHenry/FastCap parasitic extraction integration for PDN analysis
    Introduces a parasitic extraction module that converts KiCad PCB layout
    geometry into FastHenry (.inp) and FastCap (.lst/.qui) input formats,
    enabling R/L/C extraction to inform an external PDN analyzer.
    Components:
    - pdn_parasitic_data.h: Data structures (RLGC, impedance/capacitance
    matrices, extraction config) for the PDN analyzer interface
2026-02-17 Add comprehensive test suite for parasitic extraction feature
    Tests cover:
    - PDN_PARASITIC data structure defaults and initialization
    - FastHenry Zc.mat parser (single/multi port, multi frequency, scientific notation)
    - FastCap capacitance matrix parser (single/multi conductor, unit conversion)
    - DeriveLumpedParasitics (R/L/C extraction, mutual skipping, DC handling)
    - JSON serialization (empty/populated results, all field types)
2026-02-17 Add additional edge case and robustness tests for parasitic extraction
    New tests include:
    - Parser robustness: negative imaginary impedance, large 5x5 matrices
    - Physical validation: skin effect R increase, inductance consistency
    - Stackup modeling: 4-layer board construction and ordering
    - Matrix symmetry: C_ij == C_ji, Z_ij == Z_ji verification
    - JSON serialization edge cases: empty arrays, zero values, formatting
2026-02-21 Add implementation plan for Power Distribution Chart feature
    Comprehensive plan for adding a power distribution visualization panel
    to KiCad's schematic editor (eeschema). The feature analyzes schematic
    power sources, regulators, and loads to build a hierarchical power tree
    chart showing voltage rails, current budgets, and utilization warnings.
    Key aspects:
    - Read-only analysis using existing SCH_FIELD and CONNECTION_GRAPH APIs
2026-02-21 Update power distribution chart plan with sheet-based approach
    Revises the implementation plan to generate the chart as native schematic
    drawing items on a dedicated sub-sheet instead of a custom wxPanel,
    and adds ERC integration for power-related checks.
    https://claude.ai/code/session_01MaihmEZ1WApH6Hs4v51CZD
2026-02-21 Redesign power distribution model as shared foundation for PI tool suite
    Move data model and settings to common/ for cross-editor use. Add
    PIN_REFERENCE structs with pad numbers for PCB cross-referencing, return
    net identification for rail pair discovery, and JSON serialization as
    the integration contract between the power distribution chart (eeschema),
    PDN impedance analyzer (pcbnew), and FastCap/FastHenry parasitic
    extraction (pcbnew).
2026-02-21 Correct PDN analyzer relationship: JSON is enrichment, not discovery
    The PDN analyzer identifies rails independently via power_in/power_out
    pins and decoupling capacitors on those nets. It does not depend on the
    power distribution chart's JSON for rail identification.
    Updated the plan to clarify the JSON provides optional enrichment data:
    current budgets, return net confirmation, VRM parameters, and component
    classification. The PDN analyzer works without it but produces better
2026-02-21 Add concrete integration plan for PDN analyzer and FastCap/FastHenry
    The PDN analyzer (side pane in pcbnew) and FastCap/FastHenry extraction
    already exist on other branches. This revision replaces speculative
    cross-tool language with concrete integration design:
    - In-process path: model stored in PROJECT, pcbnew reads it directly
    when PDN analyzer side pane opens (no JSON roundtrip needed)
    - File-based path: JSON export for CI/automation/explicit sharing
2026-02-22 move plan to right location
2026-02-24 Rewrite plan as minimal system diagram: buses + power topology only
    Replace the comprehensive power distribution plan with a much simpler
    system diagram generator focused on two things:
    1. Bus connectivity: only buses with explicit BUS_ALIAS definitions,
    plus nets in a "System_Diagram" net class. Shows ICs and connectors
    as boxes connected by bus bars — no pin-level detail.
    2. Power topology: tree of sources → regulators → rails → loads,
2026-02-25 Add system diagram generator for bus connectivity and power topology
    Implement a 3-phase system diagram generator accessible from the Inspect
    menu in eeschema. The feature analyzes the schematic to extract bus
    connectivity (via BUS_ALIAS definitions), specially marked signals
    (nets assigned to "System_Diagram" net class), and power topology
    (from PT_POWER_IN/PT_POWER_OUT pin relationships), then generates a
    visual diagram on a dedicated sub-sheet.
2026-02-25 Split system diagram into two separate sheets
    Refactor the generator to produce two distinct sub-sheets instead of
    one combined sheet:
    - "System Connections" (system_connections.kicad_sch): bus connectivity
    and marked signal diagrams
    - "Power Distribution" (power_distribution.kicad_sch): power tree
    topology from source through regulators to loads
2026-02-25 Fix use-after-free in power tree and header/layout overlap
    Fix critical memory bug where child power nodes were owned by a local
    map in buildPowerTree(), causing use-after-free when the function
    returned. Now all power nodes are stored in m_allPowerNodes for
    ownership while m_powerRoots holds non-owning root pointers.
    Also fix layout overlap where component positions and header text both
    started at (margin, margin) by offsetting the layout origin to account
2026-02-25 Add current annotations to power distribution diagram
    Adds support for per-rail current aggregation on the system diagram's
    power distribution sheet. Components annotate their current draw using
    custom fields following the I.* dot-namespace convention (matching Sim.*):
    - I.<mode> (e.g. I.typ = 150mA) for single-rail components
    - I.<pin>.<mode> (e.g. I.VDD.typ = 100mA) for multi-rail components
    The analyzer scans all load symbols for I.* fields, parses values with
2026-02-25 Refactor current fields from I.* to Pwr.I.* namespace with pin disambiguation
    Renames the current annotation field prefix from "I." to "Pwr.I." to
    establish a single "Pwr.*" namespace for all power-related metadata.
    This enables future extensions (Pwr.Noise, Pwr.Eff, Pwr.Ripple, etc.)
    without fragmenting across multiple top-level prefixes.
    Also adds smart disambiguation for single-part suffixes: when a user
    writes "Pwr.I.VDD = 80mA", the analyzer checks whether "VDD" matches
2026-02-26 Add converter types, efficiency, and current bubble-up to power diagram
    Implement the Pwr.Type (LDO/SMPS/SWITCH), Pwr.InputPin, and Pwr.Eff.*
    field annotations for regulator symbols in the power distribution diagram.
    Data model (SD_POWER_NODE):
    - CONVERTER_TYPE enum: CONV_LDO, CONV_SMPS, CONV_SWITCH
    - Input net tracking (m_inputNetName, m_inputVoltage)
    - Efficiency per mode (m_efficiencyByMode from Pwr.Eff.* fields)
2026-02-26 Fix: include full SD_POWER_NODE definition for nested type access
    The drawBiasEdge() declaration uses SD_POWER_NODE::BIAS_CONNECTION,
    which requires the full struct definition, not just a forward declaration.
    Include system_diagram_analyzer.h in the generator header.
    https://claude.ai/code/session_01RQ41m83n67KEZHBkrV7cyP
